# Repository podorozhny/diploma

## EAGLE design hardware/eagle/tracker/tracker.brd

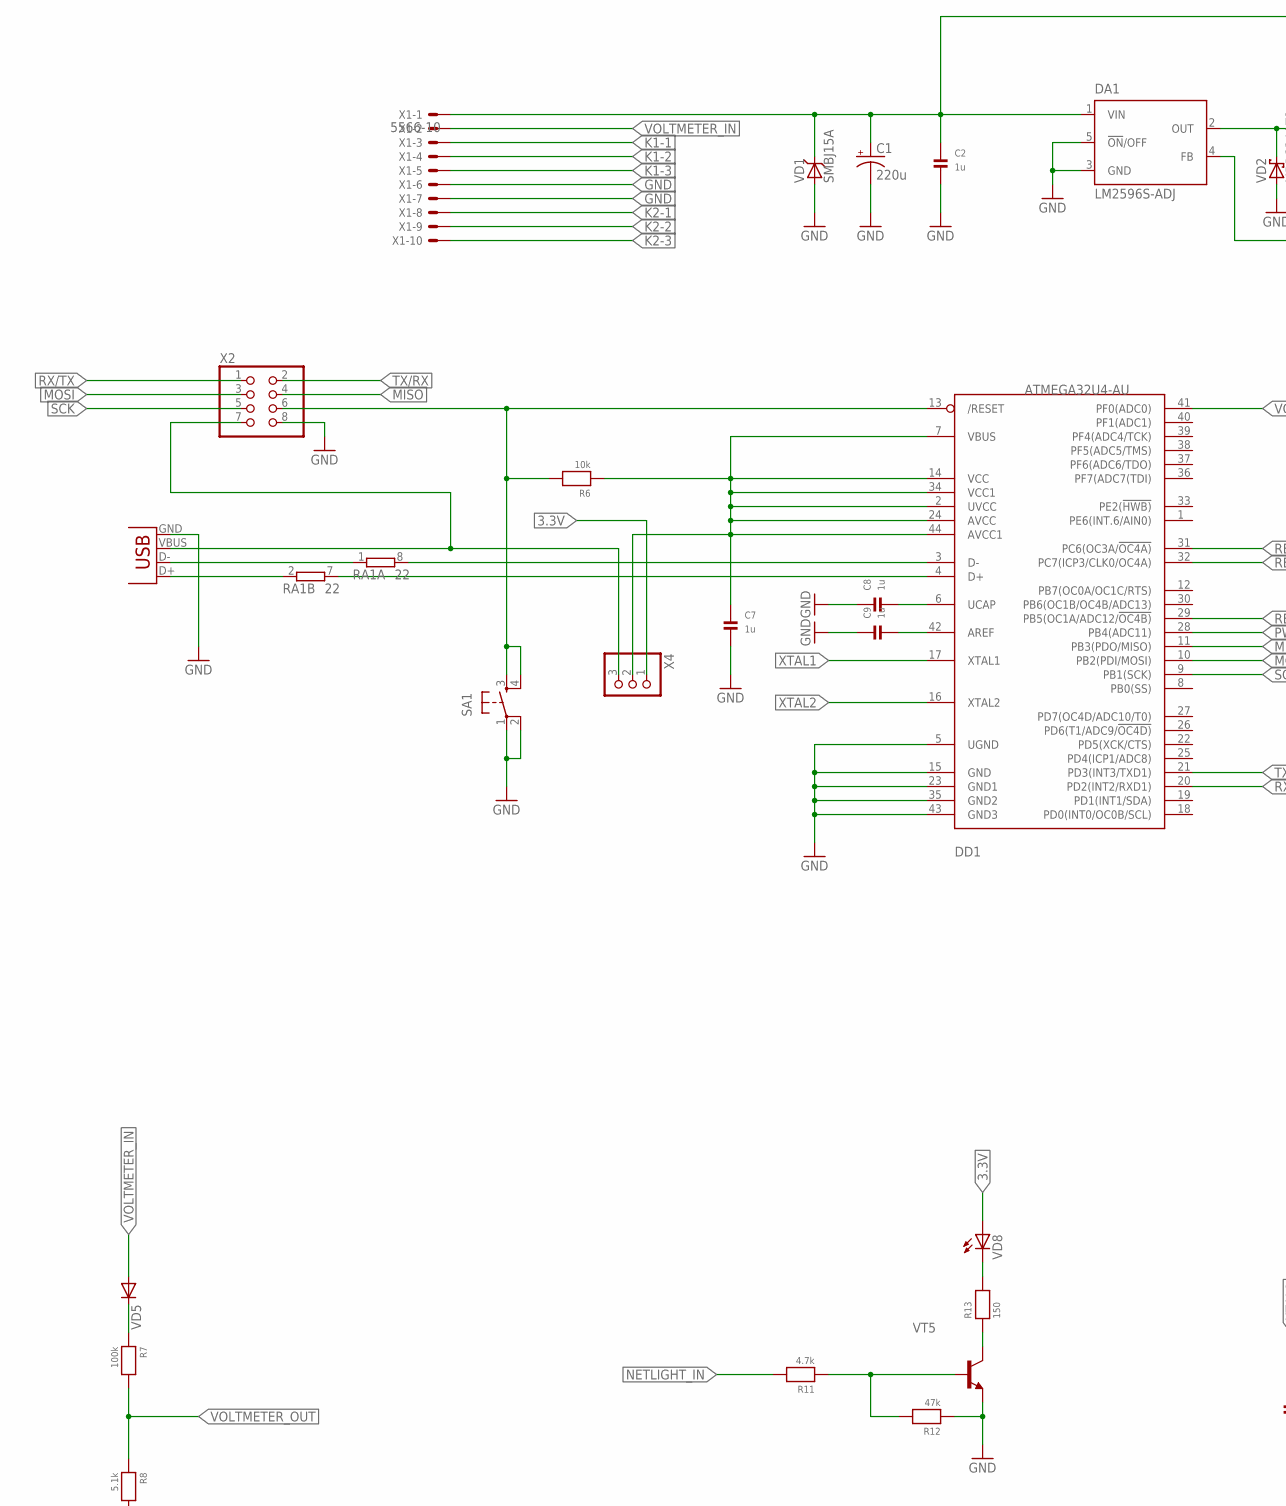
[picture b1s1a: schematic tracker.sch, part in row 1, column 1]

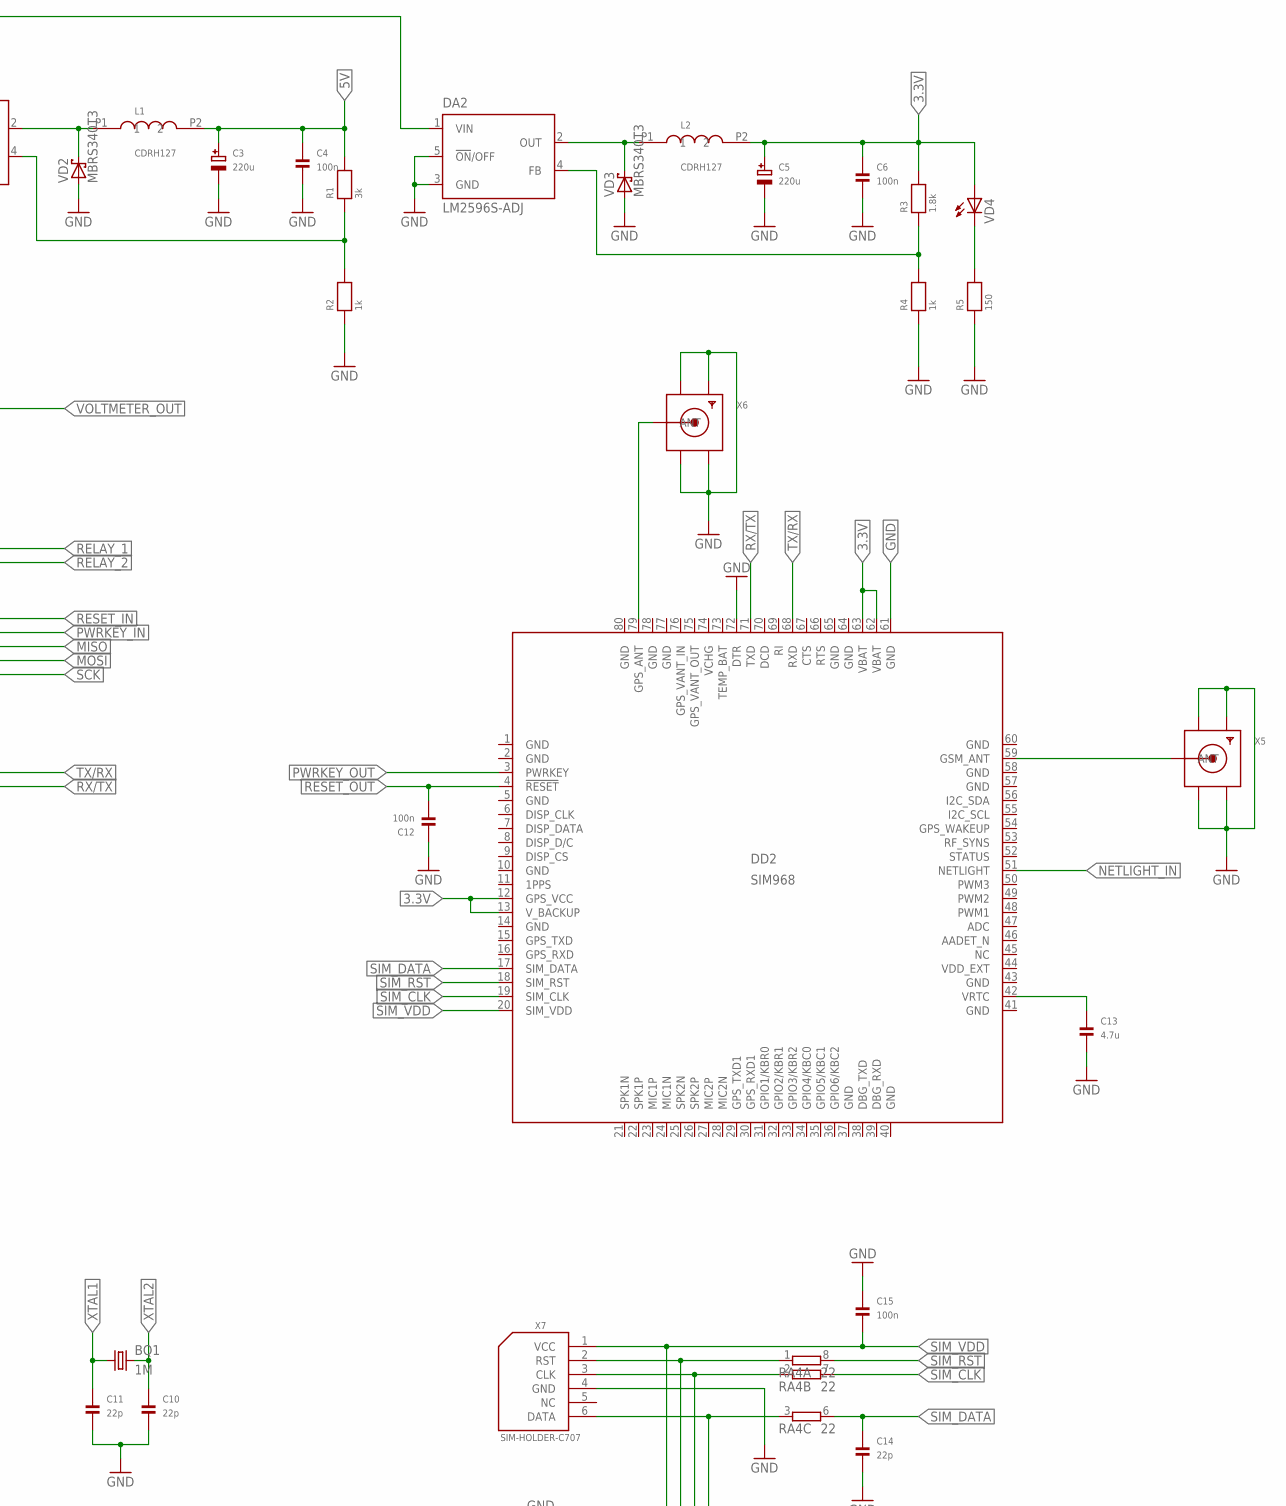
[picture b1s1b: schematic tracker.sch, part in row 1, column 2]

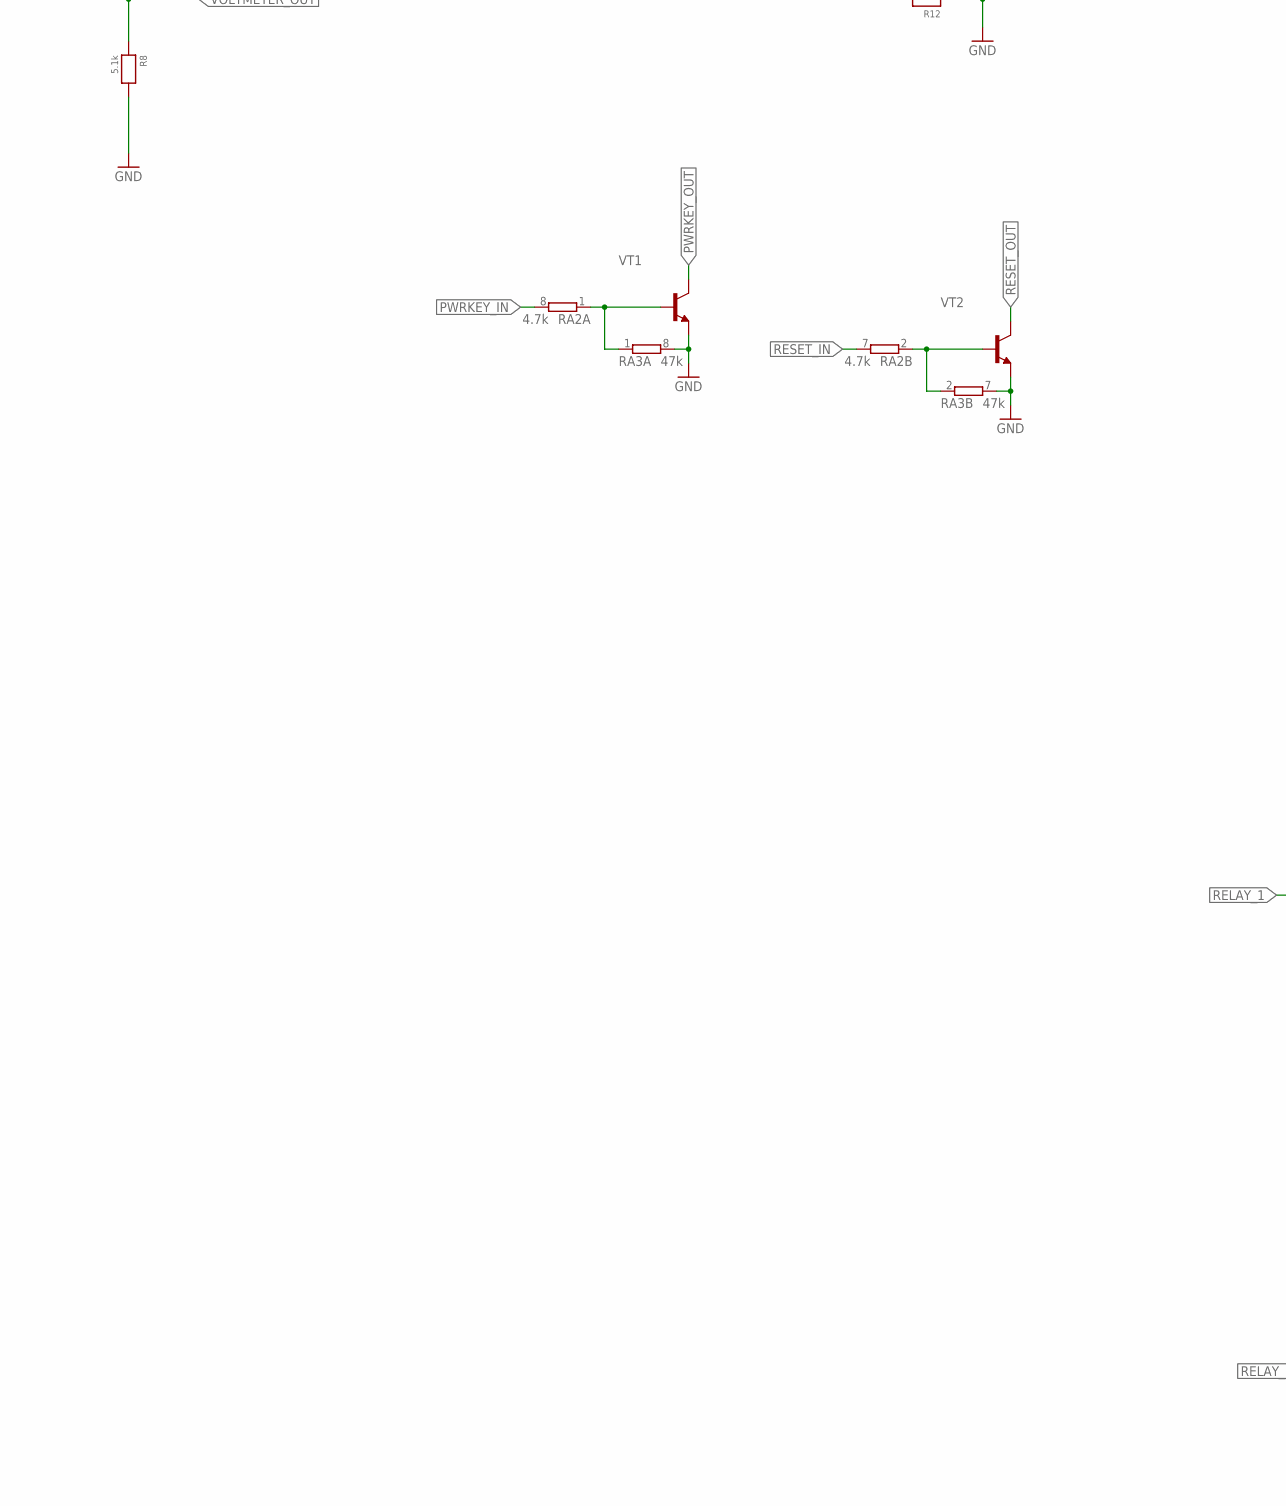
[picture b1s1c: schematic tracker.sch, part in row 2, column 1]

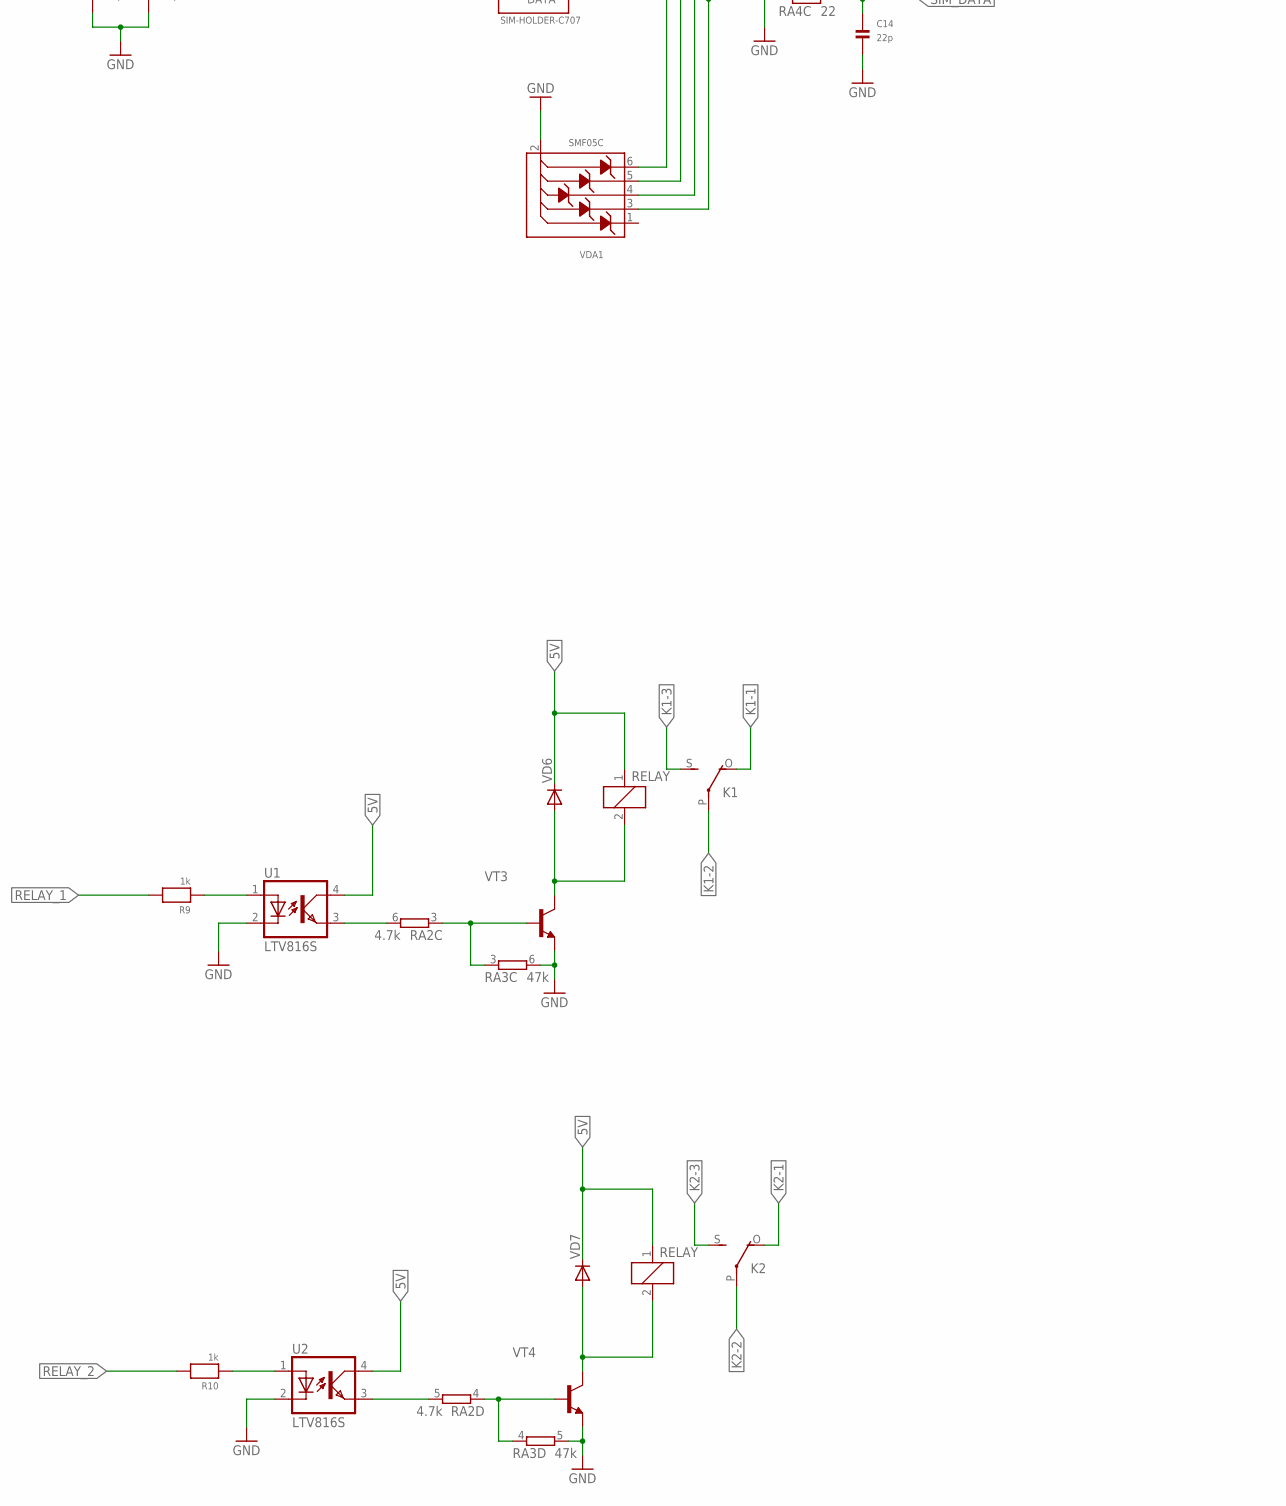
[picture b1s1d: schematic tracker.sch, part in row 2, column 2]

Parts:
BQ1: 1M; SM49
C1: 220u; PANASONIC_G
C2, C7, C8, C9: 1u; _0805
C3, C5: 220u; EIA7343-31/D-W
C4, C6, C12, C15: 100n; _0603
C10, C11, C14: 22p; _0805
C13: 4.7u; _0805
DA1, DA2: LM2596S-ADJ; TO263-5
DD1: ATMEGA32U4-AU; TQFP44
DD2: SIM968
K1, K2: RELAY
L1, L2: CDRH127
R1: 3k; _0805
R2, R4, R9, R10: 1k; _0805
R3: 1.8k; _0805
R5, R13: 150; _0805
R6: 10k; _0805
R7: 100k; _0805
R8: 5.1k; _0805
R11: 4.7k; _0805
R12: 47k; _0805
RA1, RA4: 22; CAY16
RA2: 4.7k; CAY16
RA3: 47k; CAY16
SA1: TAC_SWITCHSMD; TACTILE_SWITCH_SMD
U1, U2: LTV816S; SMD4
VD1: SMBJ15A; SMB
VD2, VD3: MBRS340T3; SMC
VD4, VD8: LEDCHIPLED_1206; CHIPLED_1206
VD5, VD6, VD7: DIODE-MELF; MELF-MLL41
VDA1: SMF05C; SC-88
VT1, VT2, VT3, VT4, VT5: BC817-40-NPN-SOT23-BEC; SOT23-BEC
X1: 5566-10
X2: PINHD-2X4; 2X04
X3: USB-B; USB-B-PTH
X4: PINHD-1X3; 1X03
X5, X6: SMACONNECTOR; SMA90_DIP
X7: SIM-HOLDER-C707

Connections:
3.3V: C5.+, C6.1, DD2.12 (GPS_VCC), DD2.13 (V_BACKUP), DD2.62 (VBAT), DD2.63 (VBAT), L2.P2 (2), R3.2, VD4.A, VD8.A, X4.1
5V: C3.+, C4.1, K1.1, K2.1, L1.P2 (2), R1.2, U1.4 (COL), U2.4 (COL), VD6.C, VD7.C
10-30V: C1.+, C2.1, DA1.1 (VIN), DA2.1 (VIN), VD1.C, X1.1
211: RA2.3 (1), RA3.3 (1), VT3.B
1241F1: R10.1, U2.1 (A)
12311: R7.1, VD5.C
23251: RA2.2 (1), RA3.2 (1), VT2.B
123111: C9.2, DD1.42 (AREF)
2112331: RA2.4 (1), RA3.4 (1), VT4.B
12112123: K1.2, VD6.A, VT3.C
234124124124: C8.2, DD1.6 (UCAP)
1241241241241: DD1.4 (D+), RA1.7 (2)
3234234234324: C7.1, DD1.2 (UVCC), DD1.7 (VBUS), DD1.14 (VCC), DD1.24 (AVCC), DD1.34 (VCC1), DD1.44 (AVCC1), R6.1, X4.2
213413241241241: DD1.3 (D-), RA1.8 (2)
EWDSFDSF3F: DA1.4 (FB), R1.1, R2.2
FDSSS33: RA2.6 (2), U1.3 (EMIT)
FDSSS333: K2.2, VD7.A, VT4.C
FSDFSSF: R9.1, U1.1 (A)
FSS34: RA2.5 (2), U2.3 (EMIT)
GND: C1.-, C2.2, C3.-, C4.2, C5.-, C6.2, C7.2, C8.1, C9.1, C10.2, C11.2, C12.1, C13.2, C14.2, C15.1, DA1.3 (GND), DA1.5 (!ON!/OFF), DA2.3 (GND), DA2.5 (!ON!/OFF), DD1.5 (UGND), DD1.15 (GND), DD1.23 (GND1), DD1.35 (GND2), DD1.43 (GND3), DD2.1 (GND), DD2.2 (GND), DD2.5 (GND), DD2.10 (GND), DD2.14 (GND), DD2.37 (GND), DD2.40 (GND), DD2.41 (GND), DD2.43 (GND), DD2.57 (GND), DD2.58 (GND), DD2.60 (GND), DD2.61 (GND), DD2.64 (GND), DD2.65 (GND), DD2.72 (DTR), DD2.77 (GND), DD2.78 (GND), DD2.80 (GND), R2.1, R4.1, R5.1, R8.2, R12.1, RA3.5 (2), RA3.6 (2), RA3.7 (2), RA3.8 (2), SA1.1, SA1.2, U1.2 (C), U2.2 (C), VD1.A, VD2.A, VD3.A, VDA1.2 (ANODE), VT1.E, VT2.E, VT3.E, VT4.E, VT5.E, X1.6, X1.7, X2.8, X3.GND, X5.GND1, X5.GND2, X5.GND3, X5.GND4, X6.GND1, X6.GND2, X6.GND3, X6.GND4, X7.4 (GND)
HJYJY: DA2.4 (FB), R3.1, R4.2
JJYU: RA4.2 (1), VDA1.4 (CATODE3), X7.3 (CLK)
K1-1: K1.O, X1.3
K1-2: K1.P, X1.4
K1-3: K1.S, X1.5
K2-1: K2.O, X1.8
K2-2: K2.P, X1.9
K2-3: K2.S, X1.10
KYUYU: RA4.3 (1), VDA1.3 (CATODE2), X7.6 (DATA)
MISO: DD1.11 (PB3(PDO/MISO)), X2.4
MOSI: DD1.10 (PB2(PDI/MOSI)), X2.3
unnamed: R5.2, VD4.C
unnamed: R13.1, VT5.C
unnamed: R13.2, VD8.C
unnamed: R11.1, R12.2, VT5.B
unnamed: RA1.1, X3.D-
unnamed: DD2.59 (GSM_ANT), X5.ANTENNA (ANT)
unnamed: RA4.1, VDA1.5 (CATODE4), X7.2 (RST)
unnamed: RA1.2 (1), X3.D+
unnamed: DD2.79 (GPS_ANT), X6.ANTENNA (ANT)
unnamed: C13.1, DD2.42 (VRTC)
unnamed: X2.7, X3.VBUS, X4.3
NETLIGHT_IN: DD2.51 (NETLIGHT), R11.2
PWRKEY_IN: DD1.28 (PB4(ADC11)), RA2.8 (2)
PWRKEY_OUT: DD2.3 (PWRKEY), VT1.C
RELAY_1: DD1.31 (PC6(OC3A/!OC4A)), R9.2
RELAY_2: DD1.32 (PC7(ICP3/CLK0/OC4A)), R10.2
RESET: DD1.13 (/RESET), R6.2, SA1.3, SA1.4, X2.6
RESET_IN: DD1.29 (PB5(OC1A/ADC12/!OC4B)), RA2.7 (2)
RESET_OUT: C12.2, DD2.4 (!RESET), VT2.C
RX/TX: DD1.20 (PD2(INT2/RXD1)), DD2.71 (TXD), X2.1
SCK: DD1.9 (PB1(SCK)), X2.5
SDSD32: RA2.1, RA3.1, VT1.B
SFFR112R1: DA2.2 (OUT), L2.P1 (1), VD3.C
SIM_CLK: DD2.19 (SIM_CLK), RA4.7 (2)
SIM_DATA: C14.1, DD2.17 (SIM_DATA), RA4.6 (2)
SIM_RST: DD2.18 (SIM_RST), RA4.8 (2)
SIM_VDD: C15.2, DD2.20 (SIM_VDD), VDA1.6 (CATODE5), X7.1 (VCC)
TEMP_BAT: DD2.73 (TEMP_BAT)
TX/RX: DD1.21 (PD3(INT3/TXD1)), DD2.68 (RXD), X2.2
VCHG: DD2.74 (VCHG)
VOLTMETER_IN: VD5.A, X1.2
VOLTMETER_OUT: DD1.41 (PF0(ADC0)), R7.2, R8.1
WF23F23F23F23: DA1.2 (OUT), L1.P1 (1), VD2.C
XTAL1: BQ1.1, C11.1, DD1.17 (XTAL1)
XTAL2: BQ1.2, C10.1, DD1.16 (XTAL2)

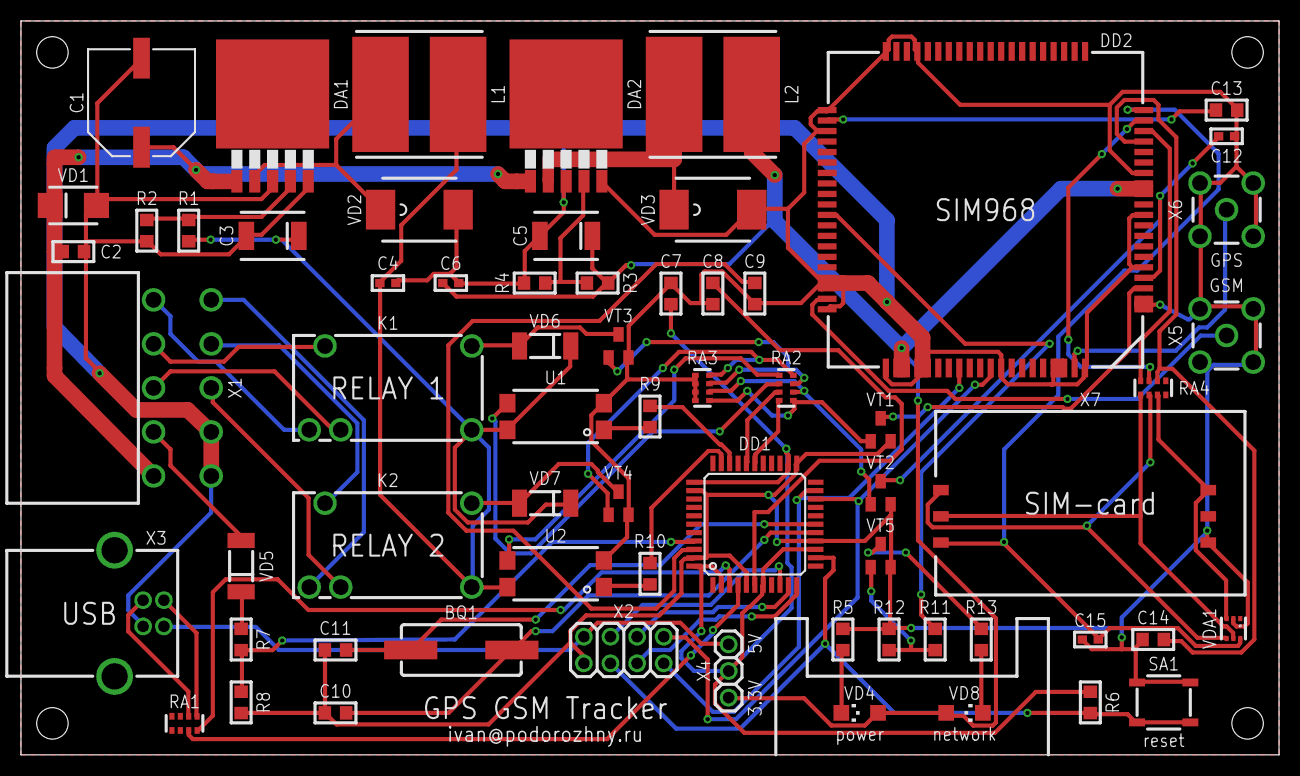
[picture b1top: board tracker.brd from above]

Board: 2 copper layers, 120.0 x 70.0 mm, 65 parts (0 on the bottom side), 64 nets.

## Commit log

2016-09-25 initial
2016-09-25 fixed filename
2016-09-25 renamed
2016-09-25 new pcb pictures
2016-09-25 schematic
2016-12-18 empty dir
2017-01-02 bunch of changes
2017-01-02 removed vendor
2017-01-02 gitignore
2017-01-02 keep

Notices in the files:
parts and their libraries:
microbuilder: This work is placed in the public domain, and may be freely used for commercial and non-commercial work with the following conditions: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
SparkFun-Connectors: Licensing: CC v3.0 Share-Alike You are welcome to use this library for commercial purposes.
